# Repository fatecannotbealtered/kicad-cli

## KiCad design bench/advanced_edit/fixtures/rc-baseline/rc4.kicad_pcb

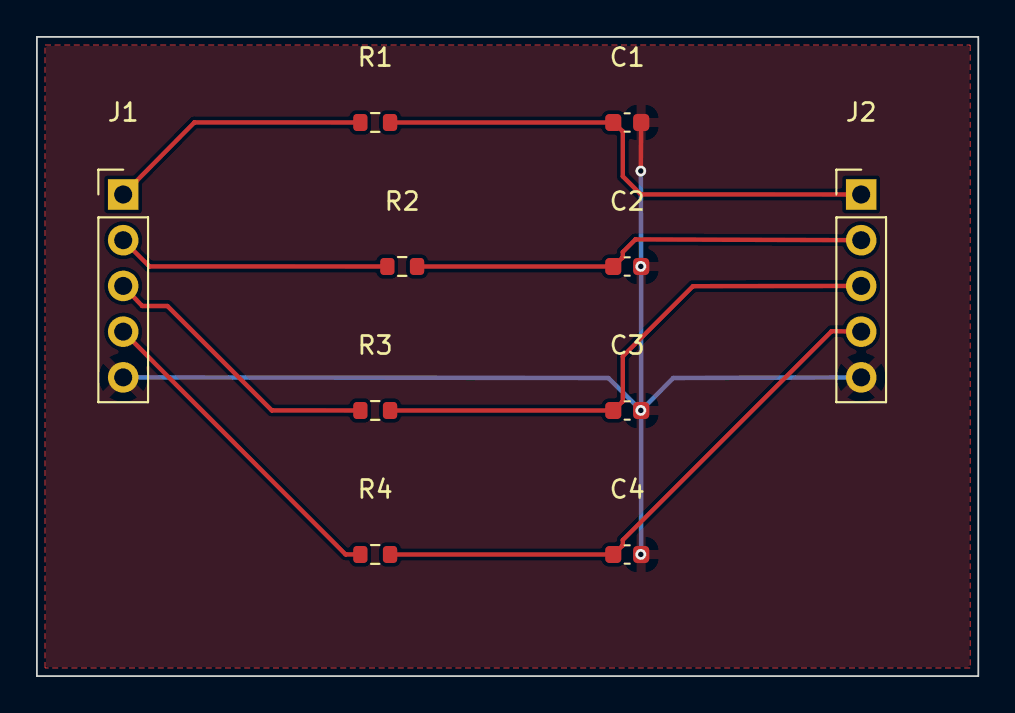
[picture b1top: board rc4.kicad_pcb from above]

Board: 2 copper layers, 52.3 x 35.5 mm, 10 parts (0 on the bottom side), 9 nets.

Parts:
C1, C3, C4: 100nF; C_0603_1608Metric
C2: 220nF; C_0603_1608Metric
J1: RC_IN; PinHeader_1x05_P2.54mm_Vertical
J2: RC_OUT; PinHeader_1x05_P2.54mm_Vertical
R1, R2, R3, R4: 1k; R_0603_1608Metric

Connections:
/IN1: J1.1, R1.1
/IN2: J1.2, R2.1
/IN3: J1.3, R3.1
/IN4: J1.4, R4.1
/OUT1: C1.1, J2.1, R1.2
/OUT2: C2.1, J2.2, R2.2
/OUT3: C3.1, J2.3, R3.2
/OUT4: C4.1, J2.4, R4.2
GND: C1.2, C2.2, C3.2, C4.2, J1.5, J2.5

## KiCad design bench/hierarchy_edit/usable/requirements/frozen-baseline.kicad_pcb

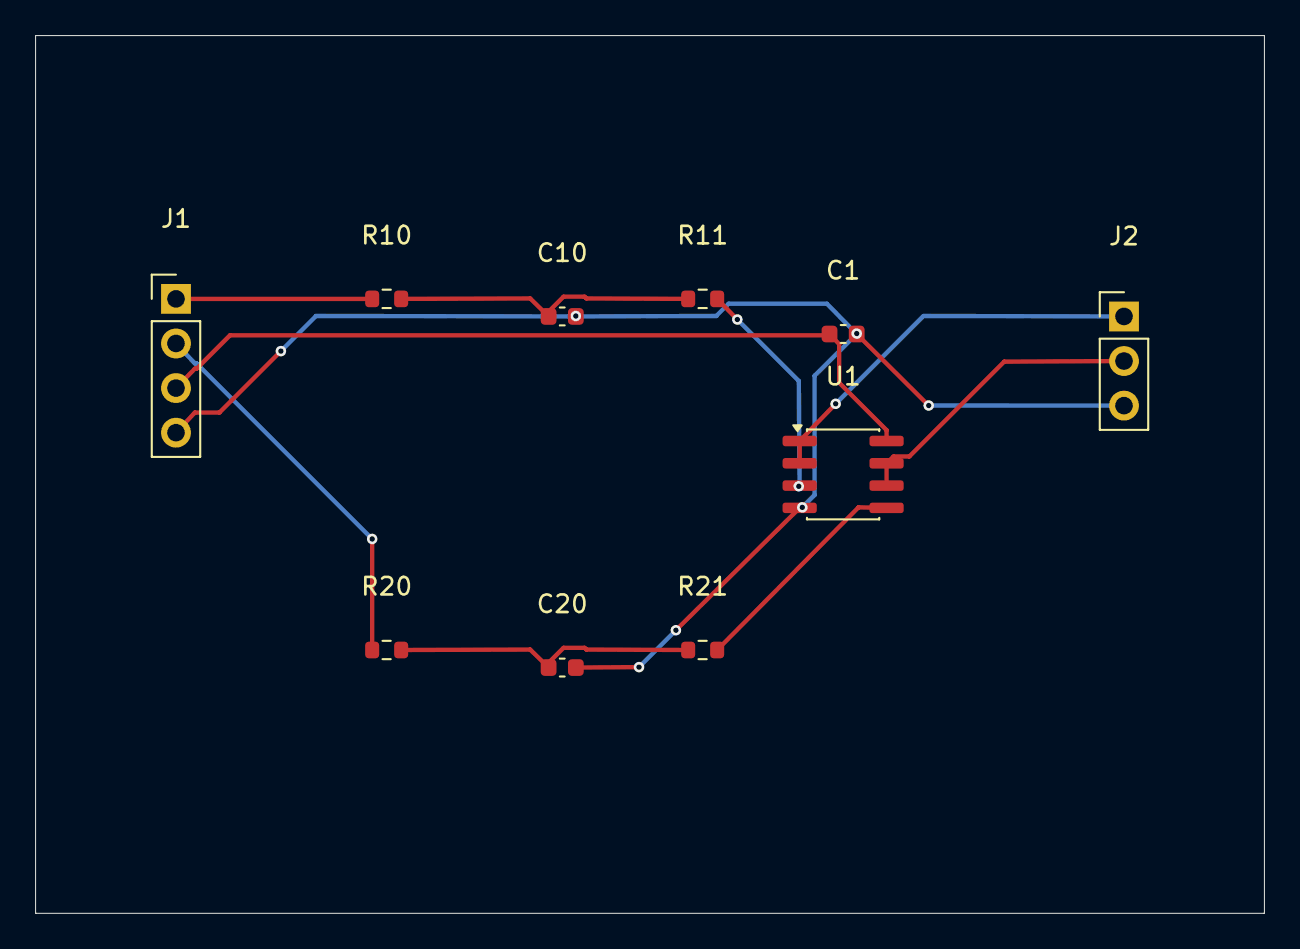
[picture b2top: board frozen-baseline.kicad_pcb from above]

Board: 2 copper layers, 70.0 x 50.0 mm, 10 parts (0 on the bottom side), 10 nets.

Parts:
C1, C10, C20: 100nF; C_0603_1608Metric
J1: IN_PWR; PinHeader_1x04_P2.54mm_Vertical
J2: BUFFER_OUT; PinHeader_1x03_P2.54mm_Vertical
R10, R20: 1k; R_0603_1608Metric
R11, R21: 100; R_0603_1608Metric
U1: LM2904; SOIC-8_3.9x4.9mm_P1.27mm

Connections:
+5V: C1.1, J1.3, U1.8
/BUF_IN_A: R11.2, U1.3
/BUF_IN_B: R21.2, U1.5
/CHILD_A/LOCAL: C10.1, R10.2, R11.1
/CHILD_B/LOCAL: C20.1, R20.2, R21.1
/IN_A: J1.1, R10.1
/IN_B: J1.2, R20.1
/OUT_A: J2.1, U1.1, U1.2
/OUT_B: J2.2, U1.6, U1.7
GND: C1.2, C10.2, C20.2, J1.4, J2.3, U1.4

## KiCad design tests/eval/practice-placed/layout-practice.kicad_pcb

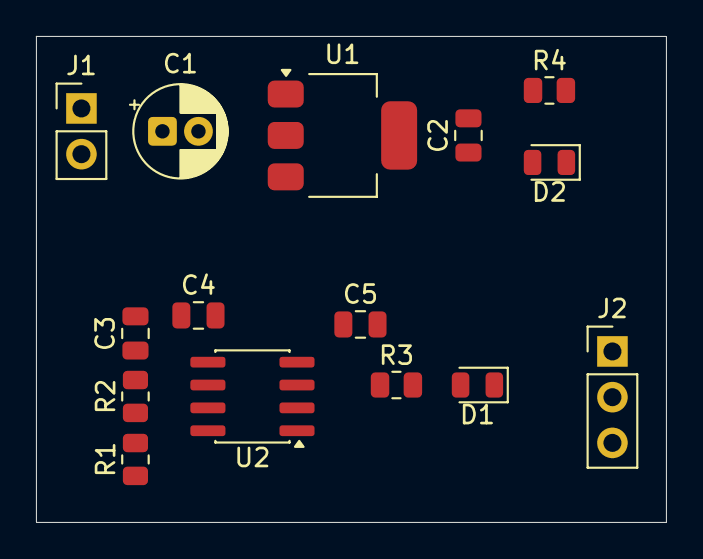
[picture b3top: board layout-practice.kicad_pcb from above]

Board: 2 copper layers, 35.0 x 27.0 mm, 15 parts (0 on the bottom side), 9 nets, no tracks yet.

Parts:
C1: 10u; CP_Radial_D5.0mm_P2.00mm
C2, C3: 10u; C_0805_2012Metric
C4: 10n; C_0805_2012Metric
C5: 100n; C_0805_2012Metric
D1: BLINK; LED_0805_2012Metric
D2: PWR; LED_0805_2012Metric
J1: PWR_IN; PinHeader_1x02_P2.54mm_Vertical
J2: OUT; PinHeader_1x03_P2.54mm_Vertical
R1: 10k; R_0805_2012Metric
R2: 47k; R_0805_2012Metric
R3: 470; R_0805_2012Metric
R4: 1k; R_0805_2012Metric
U1: AMS1117-5.0; SOT-223-3_TabPin2
U2: NE555D; SOIC-8_3.9x4.9mm_P1.27mm

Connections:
+5V: C2.1, C5.1, J2.2, R1.1, R4.1, U1.2, U2.4, U2.8
/CV: C4.1, U2.5
/DIS: R1.2, R2.1, U2.7
/LED_A: D1.2, R3.2
/OUT: J2.1, R3.1, U2.3
/PWR_LED: D2.2, R4.2
/THR: C3.1, R2.2, U2.2, U2.6
/VIN: C1.1, J1.1, U1.3
GND: C1.2, C2.2, C3.2, C4.2, C5.2, D1.1, D2.1, J1.2, J2.3, U1.1, U2.1

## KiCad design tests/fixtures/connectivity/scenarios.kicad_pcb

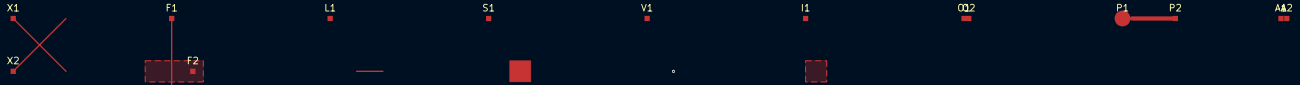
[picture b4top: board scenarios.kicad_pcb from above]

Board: 2 copper layers, 14 parts (0 on the bottom side), 5 nets.

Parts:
A1, A2: Pad
F1, F2: Pad
I1: Pad
L1: Pad
O1, O2: Pad
P1, P2: Pad
S1: Pad
V1: Pad
X1, X2: Pad

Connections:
APART: A1.1, A2.1
CROSS: X1.1, X2.1
OVERLAP: O1.1, O2.1
SHORT: P1.1, P2.1
THROUGH: F1.1, F2.1

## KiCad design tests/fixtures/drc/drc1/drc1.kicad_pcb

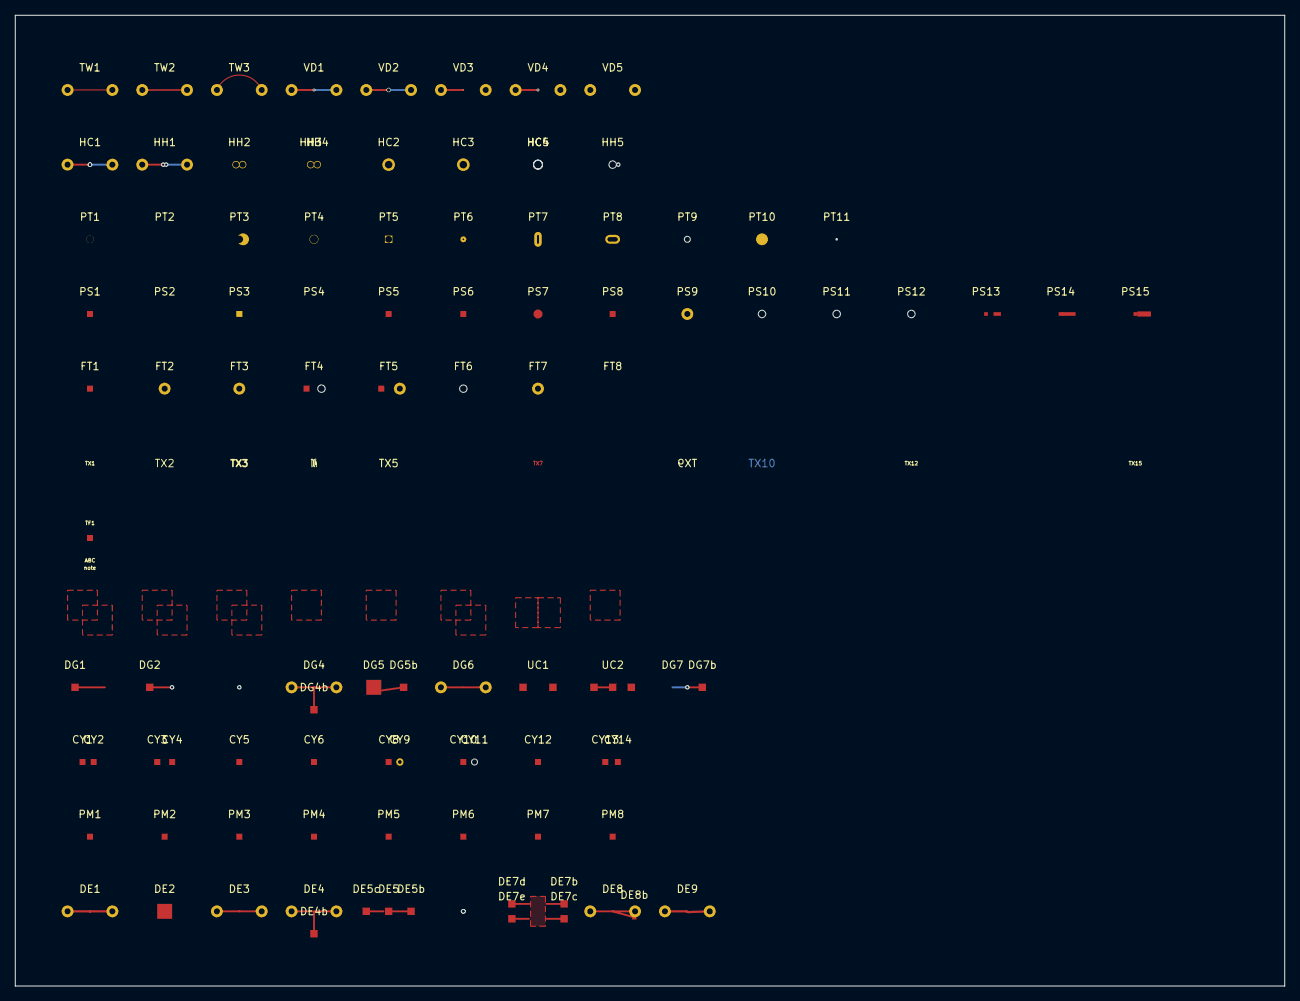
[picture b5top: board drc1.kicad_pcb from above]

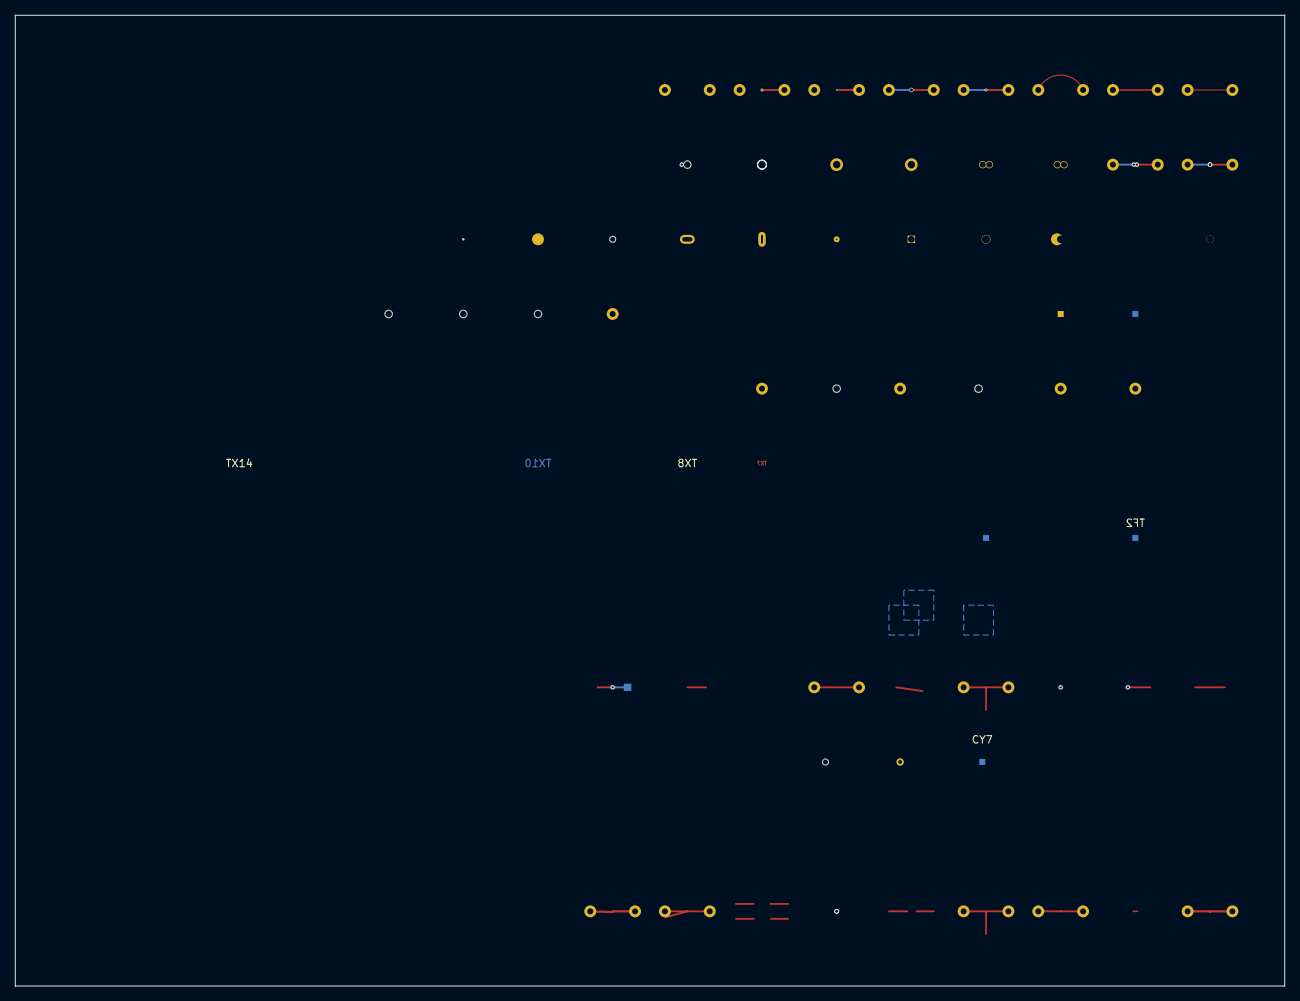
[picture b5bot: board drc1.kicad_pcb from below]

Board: 4 copper layers, 170.0 x 130.0 mm, 103 parts (3 on the bottom side), 25 nets.

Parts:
CY1: CY1
CY2: CY2
CY3: CY3
CY4: CY4
CY5: CY5
CY6: CY6
CY7: CY7
CY8: CY8
CY9: CY9
CY10: CY10
CY11: CY11
CY12: CY12
CY13: CY13
CY14: CY14
DE1: DE1
DE2: DE2
DE3: DE3
DE4: DE4
DE4b: DE4b
DE5: DE5
DE5b: DE5b
DE5c: DE5c
DE7b: DE7b
DE7c: DE7c
DE7d: DE7d
DE7e: DE7e
DE8: DE8
DE8b: DE8b
DE9: DE9
DG1: DG1
DG2: DG2
DG4: DG4
DG4b: DG4b
DG5: DG5
DG5b: DG5b
DG6: DG6
DG7: DG7
DG7b: DG7b
FT1: FT1
FT2: FT2
FT3: FT3
FT4: FT4
FT5: FT5
FT6: FT6
FT7: FT7
FT8: FT8
HC1: HC1
HC2: HC2
HC3: HC3
HC4: HC4
HC5: HC5
HH1: HH1
HH2: HH2
HH3: HH3
HH4: HH4
HH5: HH5
PM1: PM1
PM2: PM2
PM3: PM3
PM4: PM4
PM5: PM5
PM6: PM6
PM7: PM7
PM8: PM8
PS1: PS1
PS2: PS2
PS3: PS3
PS4: PS4
PS5: PS5
PS6: PS6
PS7: PS7
PS8: PS8
PS9: PS9
PS10: PS10
PS11: PS11
PS12: PS12
PS13: PS13
PS14: PS14
PS15: PS15
PT1: PT1
PT2: PT2
PT3: PT3
PT4: PT4
PT5: PT5
PT6: PT6
PT7: PT7
PT8: PT8
PT9: PT9
PT10: PT10
PT11: PT11
TF1: small; TF1
TF2: TF2
TF3: TF3
TW1: TW1
TW2: TW2
TW3: TW3
UC1: UC1
UC2: UC2
VD1: VD1
VD2: VD2
VD3: VD3
VD4: VD4
VD5: VD5

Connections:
DE1: DE1.1, DE1.2
DE3: DE3.1, DE3.2
DE4: DE4.1, DE4.2, DE4b.1
DE5: DE5.1, DE5b.1, DE5c.1
DE7: DE7b.1, DE7c.1, DE7d.1, DE7e.1
DE8: DE8.1, DE8.2, DE8b.1
DE9: DE9.1, DE9.2
DG4: DG4.1, DG4.2, DG4b.1
DG5: DG5.1, DG5b.1
DG6: DG6.1, DG6.2
DG7: DG7.1, DG7b.1
HC1: HC1.1, HC1.2
HH1: HH1.1, HH1.2
HH2: HH2.1, HH2.2
HH3: HH3.1, HH4.1
TW1: TW1.1, TW1.2
TW2: TW2.1, TW2.2
TW3: TW3.1, TW3.2
UC1: UC1.1, UC1.2
UC2: UC2.1, UC2.2, UC2.3
VD1: VD1.1, VD1.2
VD2: VD2.1, VD2.2
VD3: VD3.1, VD3.2
VD4: VD4.1, VD4.2
VD5: VD5.1, VD5.2
